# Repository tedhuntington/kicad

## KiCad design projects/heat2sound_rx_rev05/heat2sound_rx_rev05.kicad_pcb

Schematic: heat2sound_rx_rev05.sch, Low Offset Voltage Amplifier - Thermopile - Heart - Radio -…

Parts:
C1, C7, C8, C9, C10: 0.1uF; TED_SM0603_C
C2, C3, C4: 1uF; TED_SM0603_C
C5, C6: 220pF; TED_SM0603_C
C11, C12: 16pF; TED_SM0603_C
D1, D2: LED; TED_LED-1206
FB1, FB2: ferrite_bead; TED_SM0603_R
J1: TERMINAL_3.5MM_PCB_2PIN; TED_HEADER_2x1
J2: DC_2.1mm; TED_2.1mm_DC_SMD
J3, J7: JUMPER_3X1; TED_HEADER_3x1
J4: IDC_3x2; TED_IDC_3x2
J5: HEADER_3X1; TED_HEADER_3x1
J6: TERMINAL_3.5MM_PCB_2PIN; TED_TERMINAL_3.5MM_2PIN
R1, R6: 100; TED_SM0603_R
R2, R4: 100k; TED_SM0603_R
R3, R7: 10k; TED_SM0603_R
R5, R9, R10: 1k; TED_SM0603_R
R8: 1M; TED_SM0603_R
R11, R12: 250; TED_SM0603_R
S1: THERMOPILE_MLX90247; TED_HEADER_2x2_THERMO
U1: MCP6V02; SOIC-8
U2: MIC; TED_HEADER_2x1
U3: PAM8302A; MSOP-8_3x3mm_P0.65mm
U4: ATMEGA328P-AU; TQFP-32_7x7mm_Pitch0.8mm
X1: 24MHz; crystal_TSX3225

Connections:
+5v: C1.1, C4.1, C7.1, C8.1, C9.1, J2.1, J4.2, R5.1, R7.1, U1.8 (Vdd), U3.1, U3.6, U4.4, U4.6, U4.18
ADC0: R4.1, U1.7 (Out2), U4.23
ADC1: C2.2, C3.2, U4.24
GND: C1.2, C4.2, C5.2, C6.2, C7.2, C8.2, C9.2, C10.2, C11.2, C12.2, J2.2, J4.6, J5.1, R11.2, U1.4 (Vss), U2.2, U3.4, U4.3, U4.5, U4.21, X1.2, X1.4
MISO: J4.1, U4.16
MOSI: J4.4, U4.15
unnamed: C2.1, R6.2
unnamed: C3.1, R5.2, U2.1
unnamed: C5.1, FB1.1, J6.2
unnamed: C6.1, FB2.1, J6.1
unnamed: C10.1, U4.20
unnamed: C11.1, R8.2, U4.8, X1.3
unnamed: C12.1, R8.1, U4.7, X1.1
unnamed: D1.1, U4.12
unnamed: D1.2, R11.1
unnamed: FB1.2, U3.5
unnamed: FB2.2, U3.8
unnamed: J1.1, J7.1
unnamed: J1.2, J3.1
unnamed: J3.2, U1.3 (In1+)
unnamed: J3.3, S1.1
unnamed: J5.2, R9.1
unnamed: J5.3, R10.1
unnamed: J7.2, R1.2
unnamed: J7.3, S1.3
unnamed: R1.1, R2.2, U1.2 (In1-)
unnamed: R2.1, R3.1, U1.1 (Out1)
unnamed: R3.2, U1.5 (In2+)
unnamed: R4.2, U1.6 (In2-)
unnamed: R6.1, U3.3
RX: R9.2, U4.30
SCLK: J4.3, U4.17
TX: R10.2, U4.31
~RESET: J4.5, R7.2, U4.29

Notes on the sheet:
Add volume control
(running sensor + and - into + and - of amp should cancel the 60 hz of electrical mains frequency of power source but probably should use DC source)
stage 1 amplifies 1000x
for a total of 10,000x 100uv=1V
stage 2 amplifies 10x
Thermopile Out
Thermopile
external sensor
Audio Out
(for electrodes to measure heart beat, alpha wave millivolts, etc)
1.8V to 5.5V DC
heat2sound_rx
SpeakerOut
Electret Microphone
(2x1 female terminal)
(2x2 female header)
Receives sound and heat, converts into voltage and outputs on stereo output audio (left) heat (right)
ferrite bead used to filter out high freq signals
MMZ1608B121CTAH0 120ohm @100MHz
todo: add oscilloscope pins
https://en.wikipedia.org/wiki/Phone_connector_(audio)
alt amp: LM386
todo: add potentiometers
good links: https://web.ece.ucsb.edu/Faculty/rodwell/Classes/ece2c/labs/Lab1b-2C2007.pdf
was MCP6V02 MCP6N11-100E/SN MCP6N16-100E/MS
audio should be between +2v and -2v
ISP
40mA max on IO pins
IR LED

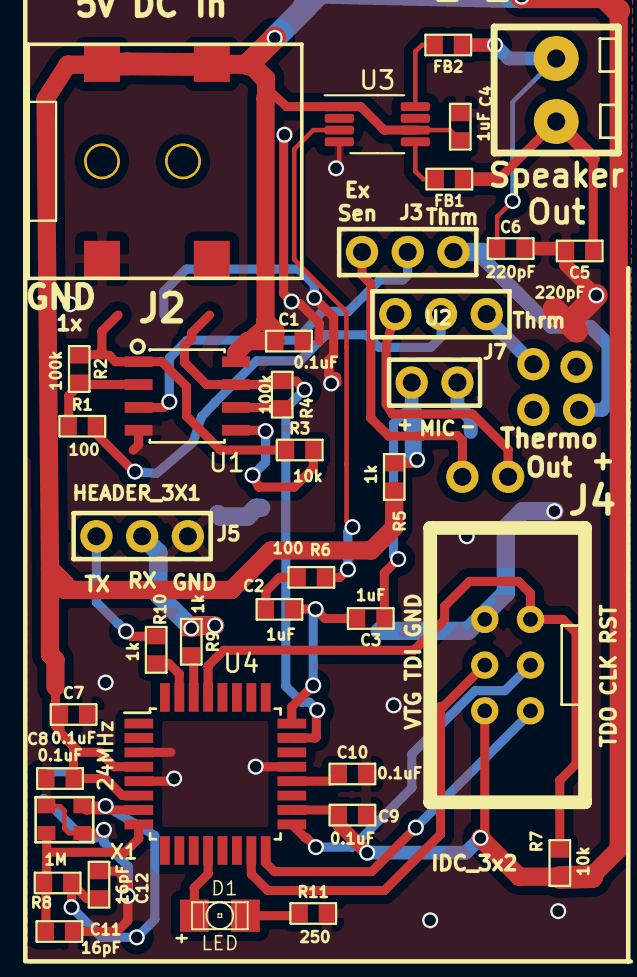
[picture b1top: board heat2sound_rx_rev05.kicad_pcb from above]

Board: 2 copper layers, 39 parts (0 on the bottom side), 34 nets.

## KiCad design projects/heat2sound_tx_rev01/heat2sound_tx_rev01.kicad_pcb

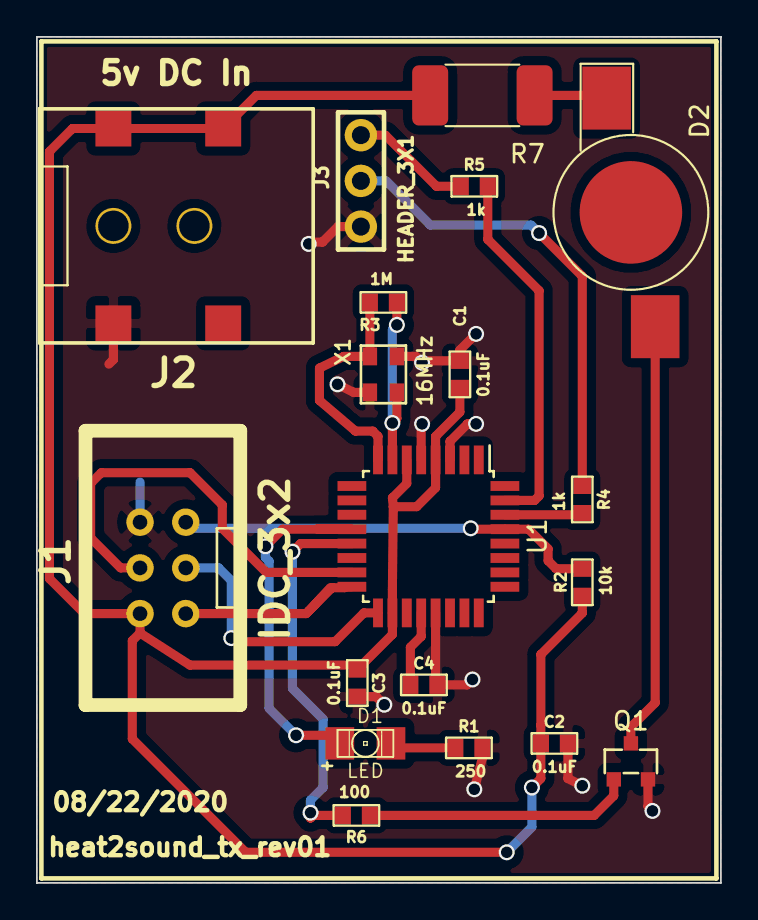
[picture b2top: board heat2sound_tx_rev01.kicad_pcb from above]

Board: 2 copper layers, 38.0 x 47.0 mm, 19 parts (0 on the bottom side), 19 nets.

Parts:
C1, C2, C3, C4: 0.1uF; TED_SM0603_C
D1: LED; TED_LED-1206
D2: LED; LED_1W_3W_R8
J1: IDC_3x2; TED_IDC_3x2
J2: DC_2.1mm; TED_2.1mm_DC_SMD
J3: HEADER_3X1; TED_HEADER_3x1
Q1: NMOSFET_GSD; TED_SOT-23
R1: 250; TED_SM0603_R
R2: 10k; TED_SM0603_R
R3: 1M; TED_SM0603_R
R4, R5: 1k; TED_SM0603_R
R6: 100; TED_SM0603_R
R7: 10; TED_R_2512_6332Metric
U1: ATMEGA328P-AU; TQFP-32_7x7mm_Pitch0.8mm
X1: 16MHz; crystal_TSX3225

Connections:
+5V: C1.1, C2.1, C3.1, J1.2, J2.1, R2.1, R7.1, U1.4, U1.6, U1.18
GND: C1.2, C2.2, C3.2, C4.2, J1.6, J2.2, J3.1, Q1.2, R1.2, U1.3, U1.5, U1.21, X1.2, X1.4
MISO: J1.1, U1.16
MOSI: J1.4, U1.15
unnamed: C4.1, U1.20
unnamed: D1.1, U1.12
unnamed: D1.2, R1.1
unnamed: D2.1, R7.2
unnamed: D2.2, Q1.3
unnamed: J3.2, R4.1
unnamed: J3.3, R5.1
unnamed: Q1.1, R6.1
unnamed: R3.1, U1.7, X1.1
unnamed: R3.2, U1.8, X1.3
PulseOut: R6.2, U1.13
RX: R4.2, U1.30
SCLK: J1.3, U1.17
TX: R5.2, U1.31
~RESET: J1.5, R2.2, U1.29

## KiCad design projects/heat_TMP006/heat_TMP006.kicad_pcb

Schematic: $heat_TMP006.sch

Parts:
C2: .1uF
J1: HEADER_3X2
R1: 10k
U1: TMP006

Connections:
+2.8v: C2.1, J1.1, R1.1, U1.A3 (V+)
ADR0: J1.3, U1.C1 (ADR0)
ADR1: J1.4, U1.B1 (ADR1)
GND: C2.2, J1.6, U1.A1 (DGND), U1.A2 (AGND)
unnamed: R1.2, U1.C2 (~DRDY)
SCL: J1.2, U1.B3 (SCL)
SDA: J1.5, U1.C3 (SDA)

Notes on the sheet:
1.95-3.6v supply voltage, 1.62-3.6v digital interface voltage

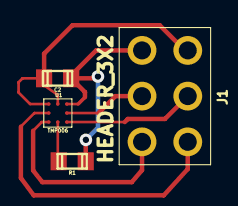
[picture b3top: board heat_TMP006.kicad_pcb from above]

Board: 2 copper layers, 4 parts (0 on the bottom side), 7 nets.

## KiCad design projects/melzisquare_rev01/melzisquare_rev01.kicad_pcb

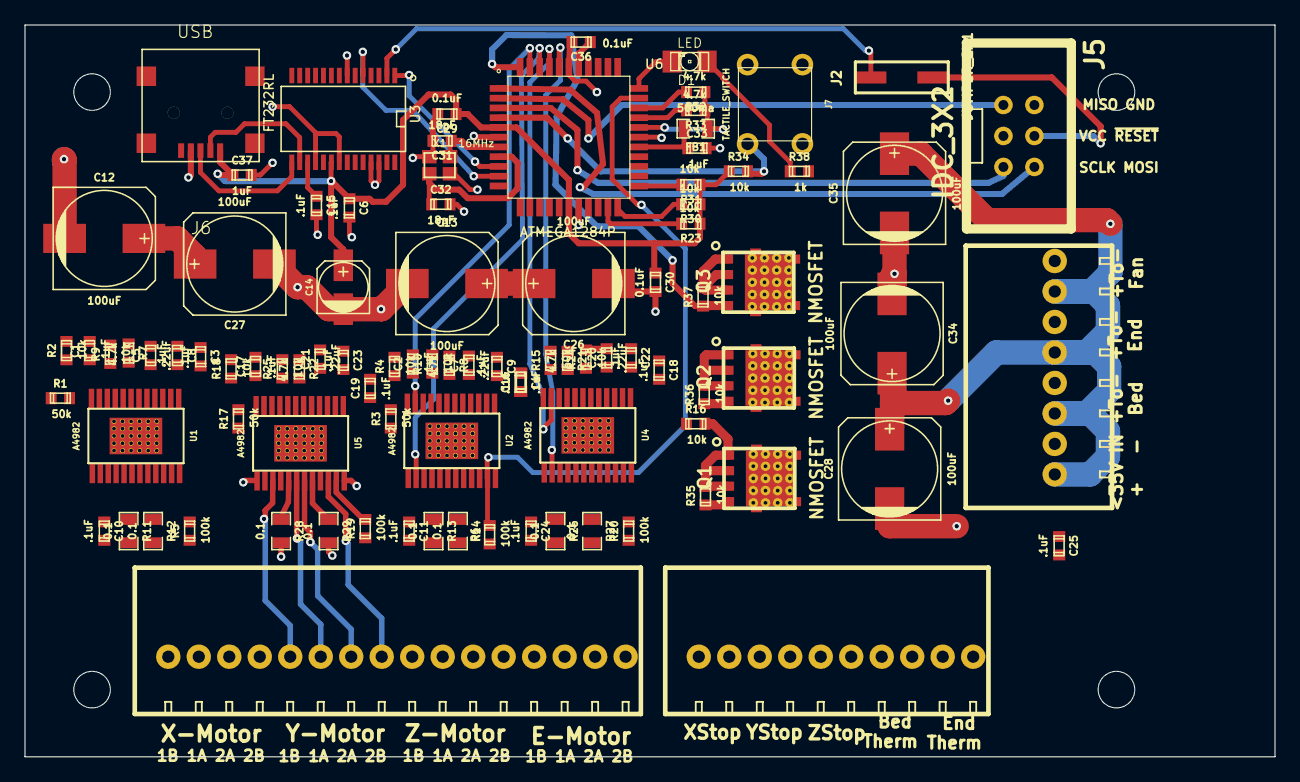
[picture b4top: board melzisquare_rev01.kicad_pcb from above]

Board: 2 copper layers, 102.5 x 60.0 mm, 98 parts (0 on the bottom side), 92 nets.

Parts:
C1, C2, C3, C4, C6, C8, C9, C10, C11, C15, C16, C17, C18, C19, C22, C23, C24, C25, C33: .1uF; TED_SM0603_C
C5, C7, C20, C21: .22uF; TED_SM0603_C
C12, C13, C26, C27, C28, C34, C35: 100uF; TED_c_elec_8mm_SMD
C14: 4.7uF; TED_c_elec_4.3x4.3
C29, C30, C36: 0.1uF; TED_SM0603_C
C31, C32: 18pF; TED_SM0603_C
C37: 1uF; TED_SM0603_C
D1: LED; LED-1206
FB1: 500ma; TED_SM0805_R
H1, H2, H3, H4: HOLE; TED_Hole_3mm
J1: TERMINAL_16X1; TED_TERMINAL_SPRING_2.54MM_16PIN_1989887
J2: JUMPER_2X1; TED_HEADER_2x1_SMT
J3: TERMINAL_10X1; TED_TERMINAL_SPRING_2.54MM_10PIN_1989829
J4: TERMINAL_8X1; TED_TERMINAL_SPRING_2.54MM_8PIN_1989803
J5: IDC_3X2; TED_IDC_3x2
J6: USB; TED_USB_SMT_MINI
J7: TACTILE_SWITCH; TED_TACTILE_SWITCH_6x6
Q1, Q2, Q3: NMOSFET; TED_SO-8_FLAT_LEAD_CASE_488AA_STYLE1
R1, R3, R15, R17: 50k; TED_SM0603_R
R2, R4, R9, R10, R16, R18, R23, R24, R25, R30, R31, R34, R35, R36, R37: 10k; TED_SM0603_R
R5, R6, R19, R20: 100k; TED_SM0603_R
R7, R8, R21, R22, R32, R33: 4.7k; TED_SM0603_R
R11, R12, R13, R14, R26, R27, R28, R29: 0.1; TED_SM0805_R
R38: 1k; TED_SM0603_R
U1, U2, U4, U5: A4982; TED_TSSOP24+PAD
U3: FT232RL; TED_SSOP28
U6: ATMEGA1284P; TED_TQFP44
X1: 16MHz; TED_crystal_FA-20H

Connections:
BED-TEMP: J3.7, R32.2, U6.31
D+: J6.3, U3.15
D-: J6.2, U3.16
E-DIR: U4.14, U6.40
E-OUT1A: J1.14, U4.18
E-OUT1B: J1.13, U4.15
E-OUT2A: J1.15, U4.19
E-OUT2B: J1.16, U4.22
E-STEP: U4.11, U6.41
END-TEMP: J3.9, R33.2, U6.30
FAN: Q3.1, R37.1, U6.44
FT_RXD: U3.5, U6.10
FT_TXD: U3.1, U6.9
GND: C1.2, C2.2, C5.2, C6.2, C7.2, C10.2, C11.2, C12.2, C13.2, C14.2, C15.2, C16.2, C17.2, C20.2, C21.2, C24.2, C25.2, C26.2, C27.2, C28.2, C29.2, C30.2, C31.2, C32.2, C33.2, C34.2, C35.2, C36.2, C37.2, J3.2, J3.4, J3.6, J3.8, J3.10, J4.2, J5.6, J6.4, J7.1, J7.2, Q1.2, Q2.2, Q3.2, R2.2, R4.2, R9.2, R10.2, R11.2, R12.2, R13.2, R14.2, R16.2, R18.2, R24.2, R25.2, R26.2, R27.2, R28.2, R29.2, R35.2, R36.2, R37.2, R38.2, U1.13, U1.24, U1.PAD, U2.13, U2.24, U2.PAD, U3.7, U3.18, U3.21, U3.25, U3.26, U4.13, U4.24, U4.PAD, U5.13, U5.24, U5.PAD, U6.6, U6.18, U6.28, U6.39, X1.2, X1.4
HOTBED: Q1.1, R35.1, U6.13
HOTEND: Q2.1, R36.1, U6.14
MISO: J5.1, U6.2
MOSI: J5.4, U6.1
unnamed: C18.2, U4.2
unnamed: C18.1, U4.1
unnamed: R21.2, U4.7, U4.9
unnamed: R24.1, U4.8
unnamed: C20.1, U4.4
unnamed: C22.2, U4.3
unnamed: R26.1, U4.17
unnamed: R15.2, R16.1, U4.12
unnamed: R27.1, U4.20
unnamed: C4.2, U2.2
unnamed: C4.1, U2.1
unnamed: R8.2, U2.7, U2.9
unnamed: R10.1, U2.8
unnamed: C7.1, U2.4
unnamed: C9.2, U2.3
unnamed: R13.1, U2.17
unnamed: R14.1, U2.20
unnamed: R3.2, R4.1, U2.12
unnamed: J4.4, Q1.3
unnamed: J4.8, Q3.3
unnamed: J4.6, Q2.3
unnamed: D1.1, R38.1
unnamed: D1.2, U6.33
unnamed: C33.1, FB1.2, U6.27
unnamed: J7.3, J7.4, R34.2, U6.4
unnamed: J2.1, U3.2
unnamed: C15.1, U3.17
unnamed: C32.1, U6.8, X1.1
unnamed: C31.1, U6.7, X1.3
unnamed: R9.1, U1.8
unnamed: C5.1, U1.4
unnamed: C8.2, U1.3
unnamed: R11.1, U1.17
unnamed: C19.1, U5.1
unnamed: C19.2, U5.2
unnamed: R22.2, U5.7, U5.9
unnamed: C23.2, U5.3
unnamed: R29.1, U5.20
unnamed: R25.1, U5.8
unnamed: C21.1, U5.4
unnamed: R28.1, U5.17
unnamed: R17.2, R18.1, U5.12
unnamed: C3.1, U1.1
unnamed: C3.2, U1.2
unnamed: R7.2, U1.7, U1.9
unnamed: R12.1, U1.20
unnamed: R1.2, R2.1, U1.12
SCLK: J5.3, U6.3
VCC: C1.1, C2.1, C6.1, C14.1, C16.1, C17.1, C29.1, C30.1, C36.1, C37.1, FB1.1, J5.2, J6.1, R1.1, R3.1, R5.1, R6.1, R7.1, R8.1, R15.1, R17.1, R19.1, R20.1, R21.1, R22.1, R23.1, R30.1, R31.1, R32.1, R33.1, R34.1, U1.5, U1.6, U1.10, U2.5, U2.6, U2.10, U3.20, U4.5, U4.6, U4.10, U5.5, U5.6, U5.10, U6.5, U6.17, U6.29, U6.38
VMotor: C8.1, C9.1, C10.1, C11.1, C12.1, C13.1, C22.1, C23.1, C24.1, C25.1, C26.1, C27.1, C28.1, C34.1, C35.1, J4.1, J4.3, J4.5, J4.7, U1.16, U1.21, U2.16, U2.21, U4.16, U4.21, U5.16, U5.21
X-DIR: U1.14, U6.24
X-OUT1A: J1.2, U1.18
X-OUT1B: J1.1, U1.15
X-OUT2A: J1.3, U1.19
X-OUT2B: J1.4, U1.22
X-STEP: U1.11, U6.16
X-STOP: J3.1, R23.2, U6.21
Y-DIR: U5.14, U6.26
Y-OUT1A: J1.6, U5.18
Y-OUT1B: J1.5, U5.15
Y-OUT2A: J1.7, U5.19
Y-OUT2B: J1.8, U5.22
Y-STEP: U5.11, U6.25
Y-STOP: J3.3, R30.2, U6.22
Z-DIR: U2.14, U6.42
Z-OUT1A: J1.10, U2.18
Z-OUT1B: J1.9, U2.15
Z-OUT2A: J1.11, U2.19
Z-OUT2B: J1.12, U2.22
Z-STEP: U2.11, U6.43
Z-STOP: J3.5, R31.2, U6.23
~RESET: J2.2, J5.5
~XYE-ENABLE: R5.2, R19.2, R20.2, U1.23, U4.23, U5.23, U6.15
~Z-ENABLE: R6.2, U2.23, U6.32

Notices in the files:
projects/melzisquare_rev01/melzisquare_rev01.kicad_pcb:
MelziSquare  rev01 05/25/2015  License: GPL
